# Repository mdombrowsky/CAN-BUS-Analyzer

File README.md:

# CAN BUS Analyzer

The goal was to replace the obsolete Microchip APGDT002 with a modern tool that supports **CAN-FD**, adds optional **secondary bus** capability, and a clean desktop interface.

## Background

The Microchip APGDT002 seems to be a handy tool, but it's long obsolete, limited to classic CAN 2.0, and its official successor is just a sad option to say it in nice words.
Since I needed a reliable analyzer with CAN-FD support anyway, I decided to build my own.

## Features

* **CAN & CAN-FD:** Support for classical CAN (2.0A/B) and CAN Flexible Data-rate.
* **Dual-Channel (Optional):** Secondary CAN bus interface for monitoring or bridging two networks.
* **Software App:** The Software is (or will be at some point) a mix between the simple functionality Microchip provided and GUI Layout inspired by PCAN.

## Hardware

(TBD / Work in Progress)

## Software

(TBD / Work in Progress)

## Status

**Work in Progress** — Currently in development (hardware layout / firmware / software). 

## License & Usage
Just to be clear: the code and hardware designs in this repository are not open source.
They are posted for reference only and are not free to republish, duplicate, or distribute in any form, especially for commercial purposes.
If you want to use/build this for personal use, you are completely welcome to do so.

## Getting started

To make it easy for you to get started with GitLab, here's a list of recommended next steps.

Already a pro? Just edit this README.md and make it your own. Want to make it easy? [Use the template at the bottom](#editing-this-readme)!

## Add your files

- [ ] [Create](https://docs.gitlab.com/ee/user/project/repository/web_editor.html#create-a-file) or [upload](https://docs.gitlab.com/ee/user/project/repository/web_editor.html#upload-a-file) files
- [ ] [Add files using the command line](https://docs.gitlab.com/topics/git/add_files/#add-files-to-a-git-repository) or push an existing Git repository with the following command:

```
cd existing_repo
git remote add origin http://gitlab.internal.dombrowsky.online/michael/can-bus-analyzer.git
git branch -M main
git push -uf origin main
```

## Integrate with your tools

- [ ] [Set up project integrations](http://gitlab.internal.dombrowsky.online/michael/can-bus-analyzer/-/settings/integrations)

## Collaborate with your team

- [ ] [Invite team members and collaborators](https://docs.gitlab.com/ee/user/project/members/)
- [ ] [Create a new merge request](https://docs.gitlab.com/ee/user/project/merge_requests/creating_merge_requests.html)
- [ ] [Automatically close issues from merge requests](https://docs.gitlab.com/ee/user/project/issues/managing_issues.html#closing-issues-automatically)
- [ ] [Enable merge request approvals](https://docs.gitlab.com/ee/user/project/merge_requests/approvals/)
- [ ] [Set auto-merge](https://docs.gitlab.com/user/project/merge_requests/auto_merge/)

## Test and Deploy

Use the built-in continuous integration in GitLab.

- [ ] [Get started with GitLab CI/CD](https://docs.gitlab.com/ee/ci/quick_start/)
- [ ] [Analyze your code for known vulnerabilities with Static Application Security Testing (SAST)](https://docs.gitlab.com/ee/user/application_security/sast/)
- [ ] [Deploy to Kubernetes, Amazon EC2, or Amazon ECS using Auto Deploy](https://docs.gitlab.com/ee/topics/autodevops/requirements.html)
- [ ] [Use pull-based deployments for improved Kubernetes management](https://docs.gitlab.com/ee/user/clusters/agent/)
- [ ] [Set up protected environments](https://docs.gitlab.com/ee/ci/environments/protected_environments.html)

***

# Editing this README

When you're ready to make this README your own, just edit this file and use the handy template below (or feel free to structure it however you want - this is just a starting point!). Thanks to [makeareadme.com](https://www.makeareadme.com/) for this template.

## Suggestions for a good README

Every project is different, so consider which of these sections apply to yours. The sections used in the template are suggestions for most open source projects. Also keep in mind that while a README can be too long and detailed, too long is better than too short. If you think your README is too long, consider utilizing another form of documentation rather than cutting out information.

## Name
Choose a self-explaining name for your project.

## Description
Let people know what your project can do specifically. Provide context and add a link to any reference visitors might be unfamiliar with. A list of Features or a Background subsection can also be added here. If there are alternatives to your project, this is a good place to list differentiating factors.

## Badges
On some READMEs, you may see small images that convey metadata, such as whether or not all the tests are passing for the project. You can use Shields to add some to your README. Many services also have instructions for adding a badge.

## Visuals
Depending on what you are making, it can be a good idea to include screenshots or even a video (you'll frequently see GIFs rather than actual videos). Tools like ttygif can help, but check out Asciinema for a more sophisticated method.

## Installation
Within a particular ecosystem, there may be a common way of installing things, such as using Yarn, NuGet, or Homebrew. However, consider the possibility that whoever is reading your README is a novice and would like more guidance. Listing specific steps helps remove ambiguity and gets people to using your project as quickly as possible. If it only runs in a specific context like a particular programming language version or operating system or has dependencies that have to be installed manually, also add a Requirements subsection.

## Usage
Use examples liberally, and show the expected output if you can. It's helpful to have inline the smallest example of usage that you can demonstrate, while providing links to more sophisticated examples if they are too long to reasonably include in the README.

## Support
Tell people where they can go to for help. It can be any combination of an issue tracker, a chat room, an email address, etc.

## Roadmap
If you have ideas for releases in the future, it is a good idea to list them in the README.

## Contributing
State if you are open to contributions and what your requirements are for accepting them.

For people who want to make changes to your project, it's helpful to have some documentation on how to get started. Perhaps there is a script that they should run or some environment variables that they need to set. Make these steps explicit. These instructions could also be useful to your future self.

You can also document commands to lint the code or run tests. These steps help to ensure high code quality and reduce the likelihood that the changes inadvertently break something. Having instructions for running tests is especially helpful if it requires external setup, such as starting a Selenium server for testing in a browser.

## Authors and acknowledgment
Show your appreciation to those who have contributed to the project.

## License
For open source projects, say how it is licensed.

## Project status
If you have run out of energy or time for your project, put a note at the top of the README saying that development has slowed down or stopped completely. Someone may choose to fork your project or volunteer to step in as a maintainer or owner, allowing your project to keep going. You can also make an explicit request for maintainers.

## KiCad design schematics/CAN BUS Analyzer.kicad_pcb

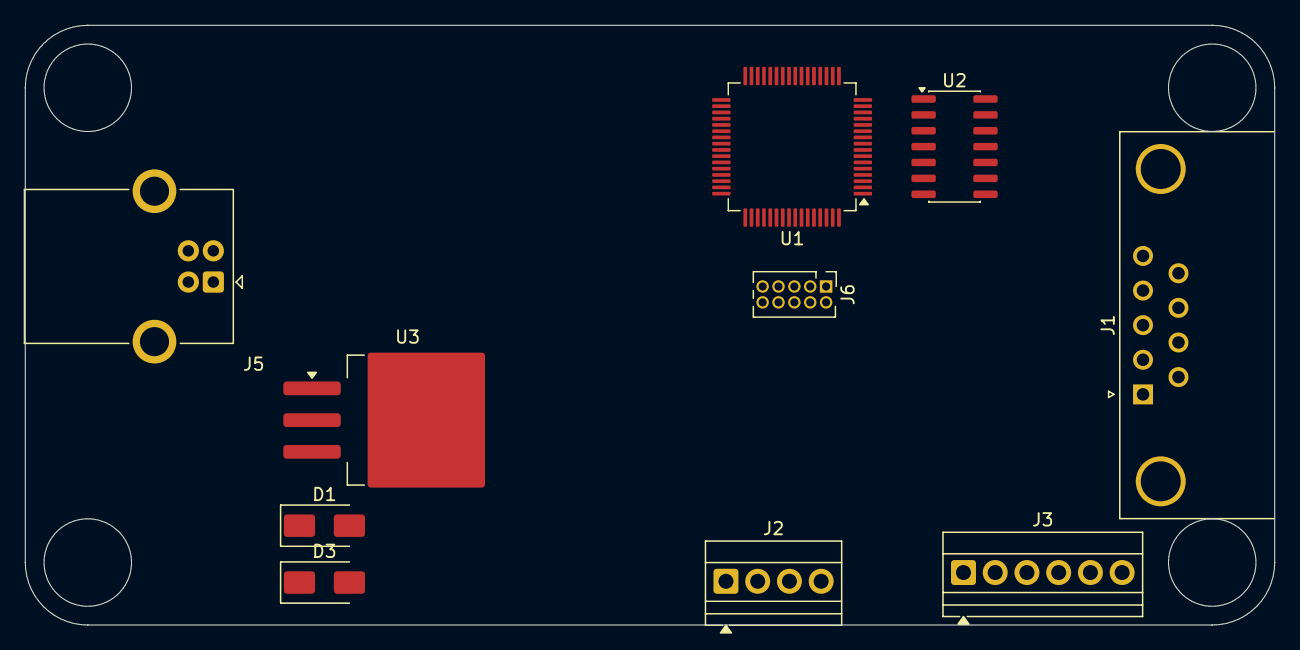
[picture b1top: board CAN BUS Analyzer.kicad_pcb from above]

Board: 2 copper layers, 100.0 x 48.0 mm, 10 parts (0 on the bottom side), 10 nets, no tracks yet.

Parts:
D1, D3: US1G; D_SMA
J1: DE9_Pins_MountingHoles; DSUB-9_Pins_Horizontal_P2.77x2.84mm_EdgePinOffset7.70mm_Hou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
J2: Conn_01x04; TerminalBlock_Xinya_XY308-2.54-4P_1x04_P2.54mm_Horizontal
J3: Conn_01x06; TerminalBlock_Xinya_XY308-2.54-6P_1x06_P2.54mm_Horizontal
J5: USB_B; USB_B_OST_USB-B1HSxx_Horizontal
J6: Conn_ARM_JTAG_SWD_10; PinHeader_2x05_P1.27mm_Vertical
U1: ATSAME51J18A-A; TQFP-64_10x10mm_P0.5mm
U2: TCAN1043xDxQ1; SOIC-14_3.9x8.7mm_P1.27mm
U3: LM2937xS; TO-263-3_TabPin2

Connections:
GND: J1.3, J1.6, J2.2, J2.3, J3.6, J5.4 (GND), U3.2 (GND)
unnamed: D3.1 (K), U3.3 (VO)
unnamed: J6.3 (GND), J6.5 (GND)
unnamed: U1.22 (GND), U1.33 (GND), U1.47 (GND), U1.54 (GND)
SWCLK: J6.4 (SWCLK/TCK), U1.57 (PA30)
SWDIO: J6.2 (SWDIO/TMS), U1.58 (PA31)
USB D+: J5.3 (D+), U1.46 (PA25)
USB D-: J5.2 (D-), U1.45 (PA24)
VCC: D1.1 (K), J3.1
VDD: D1.2 (A), U3.1 (VI)
